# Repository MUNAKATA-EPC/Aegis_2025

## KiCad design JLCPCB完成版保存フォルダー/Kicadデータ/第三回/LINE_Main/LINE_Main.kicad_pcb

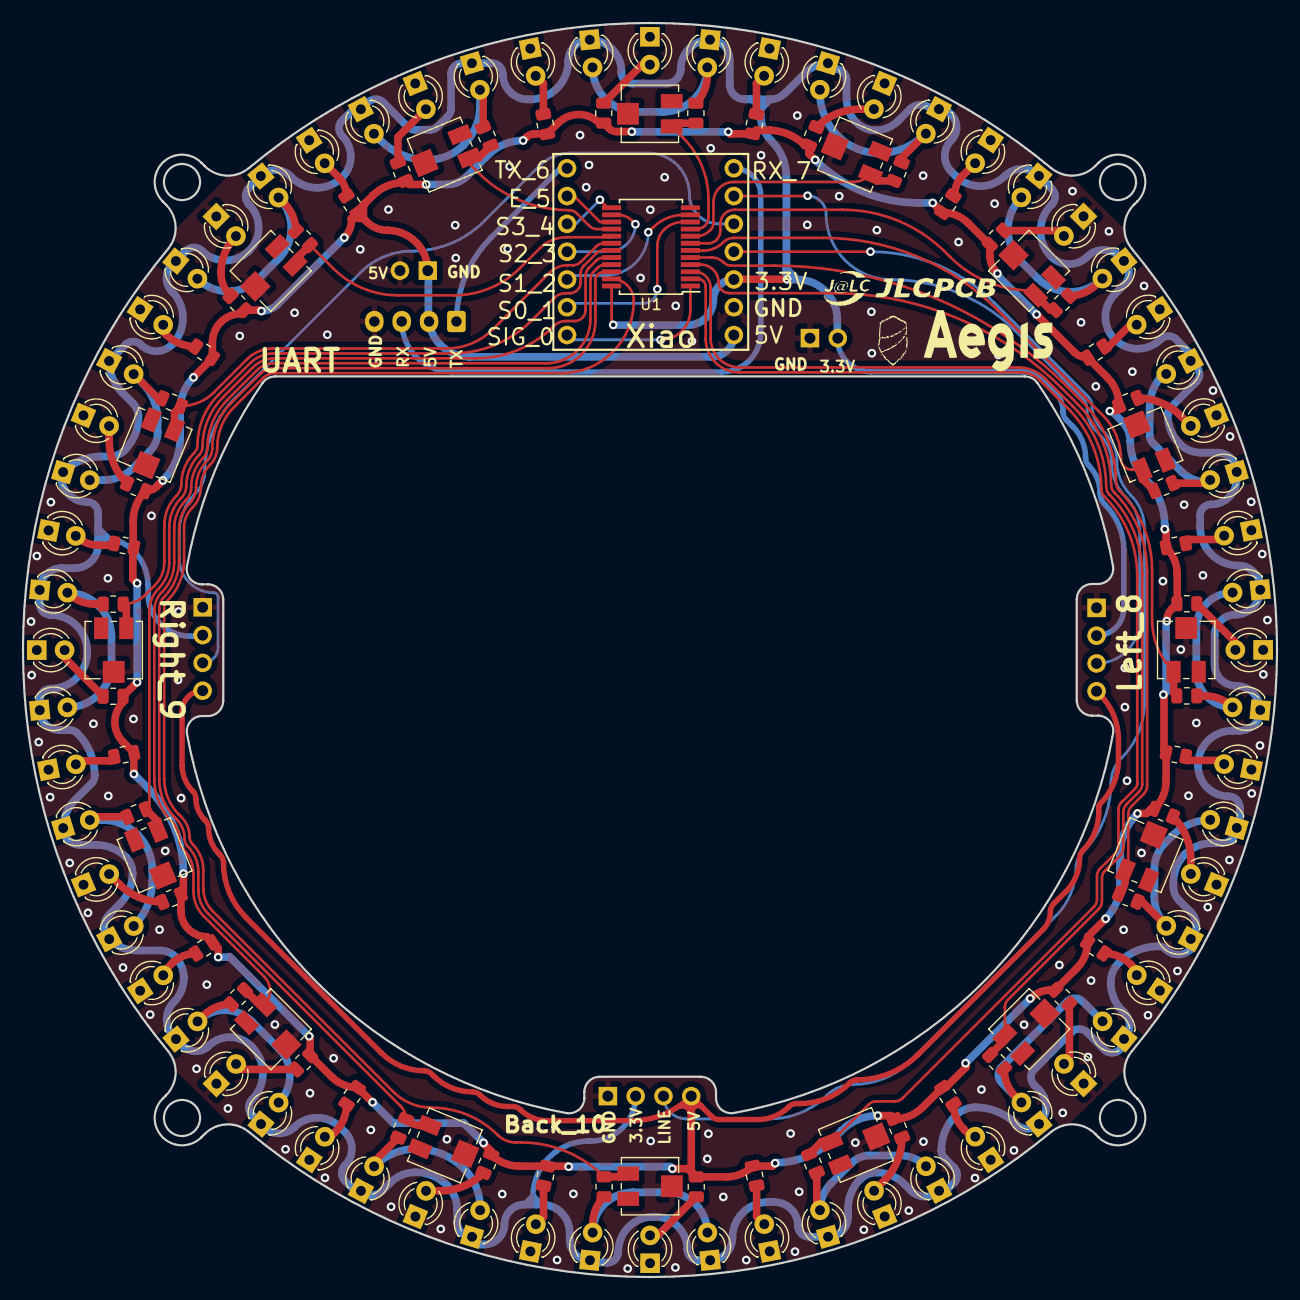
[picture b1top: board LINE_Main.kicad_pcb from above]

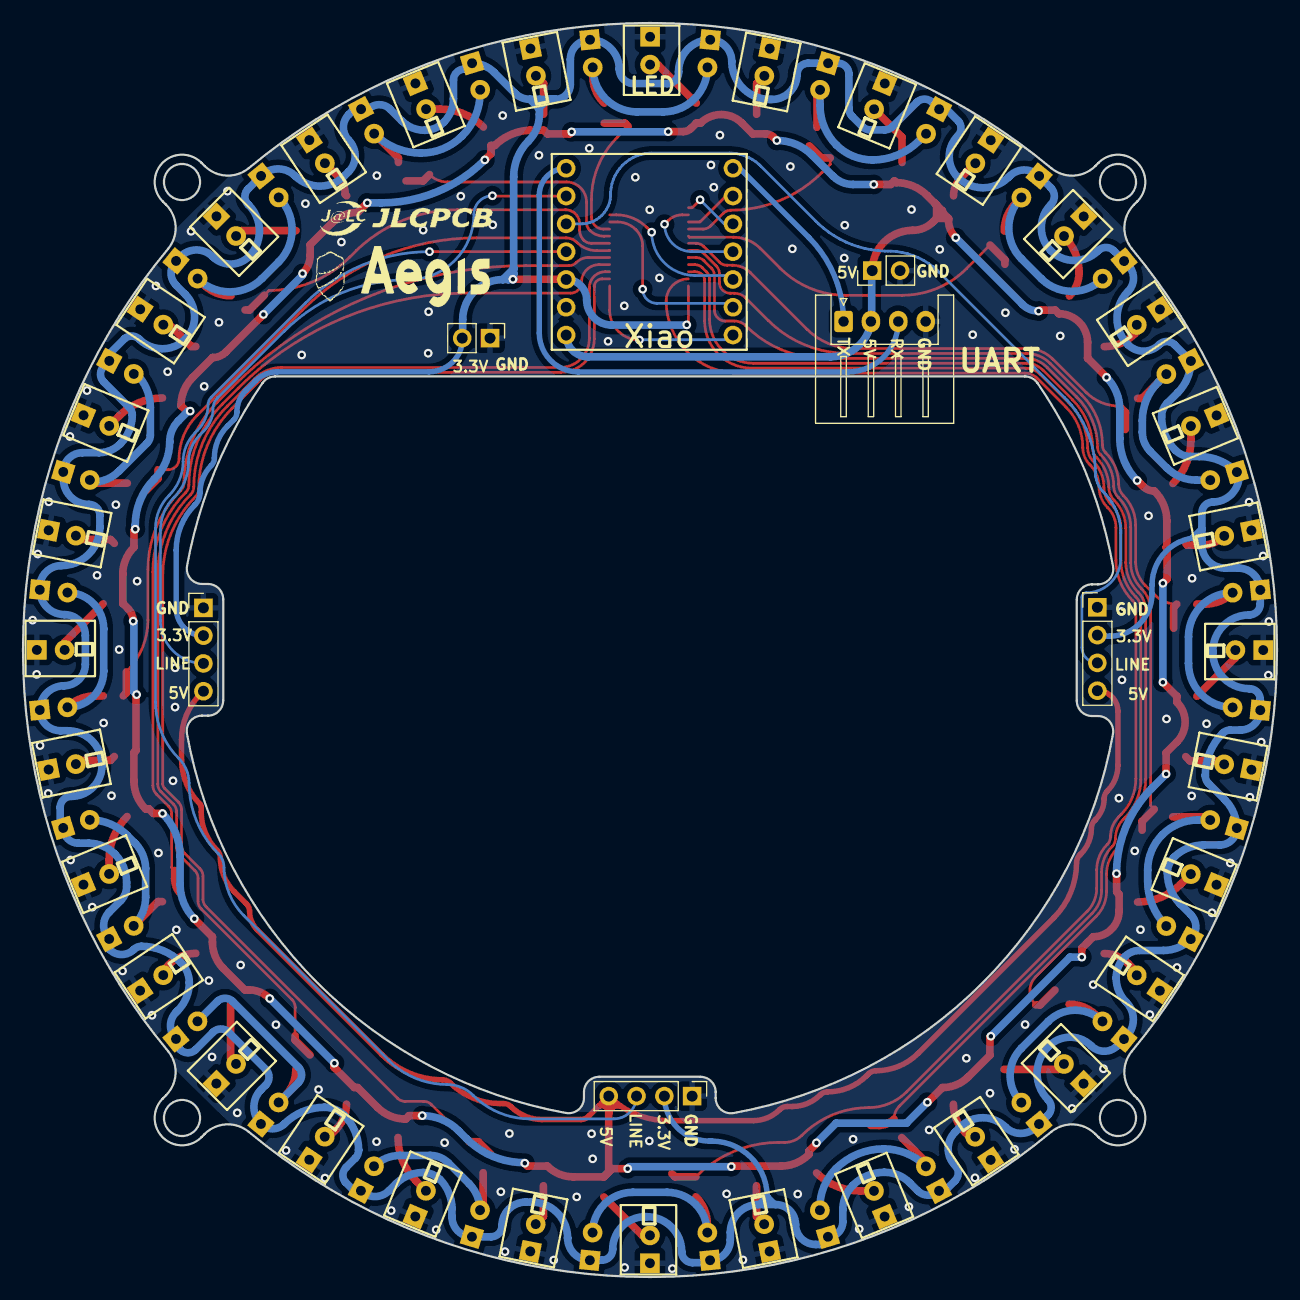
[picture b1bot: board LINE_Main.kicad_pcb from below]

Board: 2 copper layers, 114.6 x 114.6 mm, 136 parts (7 on the bottom side), 78 nets.

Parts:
C1, C2: C; PinHeader_1x02_P2.54mm_Vertical
D1, D2, D3, D4, D5, D6, D7, D8, D9, D10, D11, D12, D13, D14, D15, D16, D17, D18, D19, D20, D21, D22, D23, D24, D25, D26, D27, D28, D29, D30, D31, D32: LED; LED_D3.0mm_Clear
J1: Conn_01x04_Socket; JST_XH_S4B-XH-A_1x04_P2.50mm_Horizontal
J2, J3, J4: Conn_01x04_Socket; PinHeader_1x04_P2.54mm_Vertical
Q1, Q2, Q3, Q4, Q5, Q6, Q7, Q8, Q9, Q10, Q11, Q12, Q13, Q14, Q15, Q16, Q17, Q18, Q19, Q20, Q21, Q22, Q23, Q24, Q25, Q26, Q27, Q28, Q29, Q30, Q31, Q32: Q_Photo_NPN; LED_D3.0mm_Clear
R1, R2, R3, R4, R5, R6, R7, R8, R9, R10, R11, R12, R13, R14, R15, R16, R17, R18, R19, R20, R21, R22, R23, R24, R25, R26, R27, R28, R29, R30, R31, R32, R33, R34, R35, R36, R37, R38, R39, R40, R41, R42, R43, R44, R45, R46, R47, R48: R; R_0805_2012Metric
RV1, RV2, RV3, RV4, RV5, RV6, RV7, RV8, RV9, RV10, RV11, RV12, RV13, RV14, RV15, RV16: R_Potentiometer_Trim_US; Potentiometer_Vishay_TS53YJ_Vertical
U1: CD74HC4067SM; SSOP-24_5.3x8.2mm_P0.65mm
U2: Seeeduino_Xiao; seeeduinoXIAO

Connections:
1: R1.2, RV1.3, U1.9 (I0)
2: R2.2, RV2.3, U1.8 (I1)
3: R3.2, RV3.3, U1.7 (I2)
4: R4.2, RV4.3, U1.6 (I3)
5: R5.2, RV5.3, U1.5 (I4)
6: R6.2, RV6.3, U1.4 (I5)
7: R7.2, RV7.3, U1.3 (I6)
8: R8.2, RV8.3, U1.2 (I7)
9: R9.2, RV9.3, U1.23 (I8)
10: R10.2, RV10.3, U1.22 (I9)
11: R11.2, RV11.3, U1.21 (I10)
12: R12.2, RV12.3, U1.20 (I11)
13: R13.2, RV13.3, U1.19 (I12)
14: R14.2, RV14.3, U1.18 (I13)
15: R15.2, RV15.3, U1.17 (I14)
16: R16.2, RV16.3, U1.16 (I15)
+3.3V: C2.2, J2.2, J3.2, J4.2, Q1.1 (C), Q2.1 (C), Q3.1 (C), Q4.1 (C), Q5.1 (C), Q6.1 (C), Q7.1 (C), Q8.1 (C), Q9.1 (C), Q10.1 (C), Q11.1 (C), Q12.1 (C), Q13.1 (C), Q14.1 (C), Q15.1 (C), Q16.1 (C), Q17.1 (C), Q18.1 (C), Q19.1 (C), Q20.1 (C), Q21.1 (C), Q22.1 (C), Q23.1 (C), Q24.1 (C), Q25.1 (C), Q26.1 (C), Q27.1 (C), Q28.1 (C), Q29.1 (C), Q30.1 (C), Q31.1 (C), Q32.1 (C), U1.24 (VCC), U2.12 (3V3)
+5V: C1.1, J1.2, J2.4, J3.4, J4.4, R17.1, R18.1, R19.1, R20.1, R21.1, R22.1, R23.1, R24.1, R25.1, R26.1, R27.1, R28.1, R29.1, R30.1, R31.1, R32.1, R33.1, R34.1, R35.1, R36.1, R37.1, R38.1, R39.1, R40.1, R41.1, R42.1, R43.1, R44.1, R45.1, R46.1, R47.1, R48.1, U2.14 (5V)
Data_Line_sensor: U1.1 (COM), U2.1 (DAC)
E: U1.15 (~E), U2.6 (SCL)
GND: C1.2, C2.1, D1.1 (K), D2.1 (K), D3.1 (K), D4.1 (K), D5.1 (K), D6.1 (K), D7.1 (K), D8.1 (K), D9.1 (K), D10.1 (K), D11.1 (K), D12.1 (K), D13.1 (K), D14.1 (K), D15.1 (K), D16.1 (K), D17.1 (K), D18.1 (K), D19.1 (K), D20.1 (K), D21.1 (K), D22.1 (K), D23.1 (K), D24.1 (K), D25.1 (K), D26.1 (K), D27.1 (K), D28.1 (K), D29.1 (K), D30.1 (K), D31.1 (K), D32.1 (K), J1.4, J2.1, J3.1, J4.1, RV1.2, RV2.2, RV3.2, RV4.2, RV5.2, RV6.2, RV7.2, RV8.2, RV9.2, RV10.2, RV11.2, RV12.2, RV13.2, RV14.2, RV15.2, RV16.2, U1.12 (GND), U2.13 (GND)
Line_RX: J1.3, U2.8 (RX)
Line_TX: J1.1, U2.7 (TX)
unnamed: D1.2 (A), R17.2
unnamed: D2.2 (A), R18.2
unnamed: D3.2 (A), R19.2
unnamed: D4.2 (A), R20.2
unnamed: D5.2 (A), R21.2
unnamed: D6.2 (A), R22.2
unnamed: D7.2 (A), R23.2
unnamed: D8.2 (A), R24.2
unnamed: D9.2 (A), R25.2
unnamed: D10.2 (A), R26.2
unnamed: D11.2 (A), R27.2
unnamed: D12.2 (A), R28.2
unnamed: D13.2 (A), R29.2
unnamed: D14.2 (A), R30.2
unnamed: D15.2 (A), R31.2
unnamed: D16.2 (A), R32.2
unnamed: D17.2 (A), R33.2
unnamed: D18.2 (A), R34.2
unnamed: D19.2 (A), R35.2
unnamed: D20.2 (A), R36.2
unnamed: D21.2 (A), R37.2
unnamed: D22.2 (A), R38.2
unnamed: D23.2 (A), R39.2
unnamed: D24.2 (A), R40.2
unnamed: D25.2 (A), R41.2
unnamed: D26.2 (A), R42.2
unnamed: D27.2 (A), R43.2
unnamed: D28.2 (A), R44.2
unnamed: D29.2 (A), R45.2
unnamed: D30.2 (A), R46.2
unnamed: D31.2 (A), R47.2
unnamed: D32.2 (A), R48.2
unnamed: Q1.2 (E), Q2.2 (E), R1.1
unnamed: Q3.2 (E), Q4.2 (E), R2.1
unnamed: Q5.2 (E), Q6.2 (E), R3.1
unnamed: Q7.2 (E), Q8.2 (E), R4.1
unnamed: Q9.2 (E), Q10.2 (E), R5.1
unnamed: Q11.2 (E), Q12.2 (E), R6.1
unnamed: Q13.2 (E), Q14.2 (E), R7.1
unnamed: Q15.2 (E), Q16.2 (E), R8.1
unnamed: Q17.2 (E), Q18.2 (E), R9.1
unnamed: Q19.2 (E), Q20.2 (E), R10.1
unnamed: Q21.2 (E), Q22.2 (E), R11.1
unnamed: Q23.2 (E), Q24.2 (E), R12.1
unnamed: Q25.2 (E), Q26.2 (E), R13.1
unnamed: Q27.2 (E), Q28.2 (E), R14.1
unnamed: Q29.2 (E), Q30.2 (E), R15.1
unnamed: Q31.2 (E), Q32.2 (E), R16.1
S0: U1.10 (S0), U2.2
S1: U1.11 (S1), U2.3
S3: U1.14 (S2), U2.4
S4: U1.13 (S3), U2.5 (SDA)
Sensor_Back: J2.3, U2.11 (MOSI)
Sensor_Left: J4.3, U2.9 (SCK)
Sensor_Right: J3.3, U2.10 (MISO)

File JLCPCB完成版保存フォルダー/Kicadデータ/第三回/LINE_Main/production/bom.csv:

Designator,Footprint,Quantity,Value,LCSC Part #
"C1, C2",PinHeader_1x02_P2.54mm_Vertical,2,C,
"D1, D10, D11, D12, D13, D14, D15, D16, D17, D18, D19, D2, D20, D21, D22, D23, D24, D25, D26, D27, D28, D29, D3, D30, D31, D32, D4, D5, D6, D7, D8, D9",LED_D3.0mm_Clear,32,LED,
J1,JST_XH_S4B-XH-A_1x04_P2.50mm_Horizontal,1,Conn_01x04_Socket,
"J2, J3, J4",PinHeader_1x04_P2.54mm_Vertical,3,Conn_01x04_Socket,
"Q1, Q10, Q11, Q12, Q13, Q14, Q15, Q16, Q17, Q18, Q19, Q2, Q20, Q21, Q22, Q23, Q24, Q25, Q26, Q27, Q28, Q29, Q3, Q30, Q31, Q32, Q4, Q5, Q6, Q7, Q8, Q9",LED_D3.0mm_Clear,32,Q_Photo_NPN,
"R1, R10, R11, R12, R13, R14, R15, R16, R17, R18, R19, R2, R20, R21, R22, R23, R24, R25, R26, R27, R28, R29, R3, R30, R31, R32, R33, R34, R35, R36, R37, R38, R39, R4, R40, R41, R42, R43, R44, R45, R46, R47, R48, R5, R6, R7, R8, R9",0805,48,R,
"RV1, RV10, RV11, RV12, RV13, RV14, RV15, RV16, RV2, RV3, RV4, RV5, RV6, RV7, RV8, RV9",Potentiometer_Vishay_TS53YJ_Vertical,16,R_Potentiometer_Trim_US,
U1,SSOP-24_5.3x8.2mm_P0.65mm,1,CD74HC4067SM,
U2,seeeduinoXIAO,1,Seeeduino_Xiao,

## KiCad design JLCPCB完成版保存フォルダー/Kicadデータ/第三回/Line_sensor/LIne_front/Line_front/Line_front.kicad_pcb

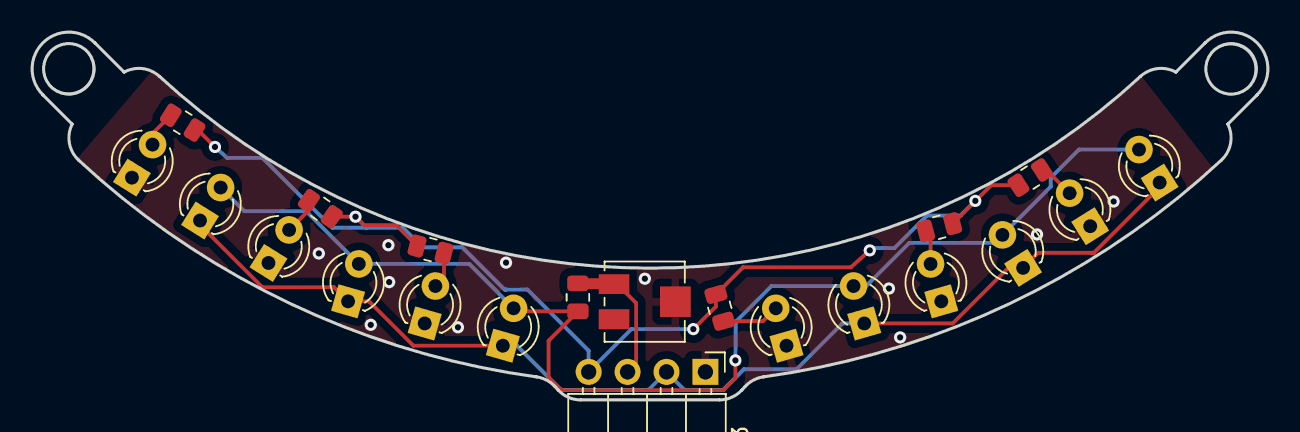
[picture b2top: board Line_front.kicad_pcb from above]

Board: 2 copper layers, 80.7 x 24.0 mm, 21 parts (0 on the bottom side), 11 nets.

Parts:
D1, D2, D2#2, D3, D4, D7: LED; LED_D3.0mm_Clear
J3: Conn_01x04_Socket; PinHeader_1x04_P2.54mm_Horizontal
Q1, Q3, Q4, Q15, Q16, Q17: Q_Photo_NPN; LED_D3.0mm_Clear
R1, R1#2, R2, R4, R5, R6, R7: R; R_0805_2012Metric
RV2: R_Potentiometer_Trim_US; Potentiometer_Vishay_TS53YJ_Vertical

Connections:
+3.3V: J3.2, Q1.1 (C), Q3.1 (C), Q4.1 (C), Q15.1 (C), Q16.1 (C), Q17.1 (C)
+5V: J3.4, R1.1, R1#2.1, R2.1, R5.1, R6.1, R7.1
Data_Line_sensor: J3.3, R4.2, RV2.3
GND: D1.1 (K), D2.1 (K), D2#2.1 (K), D3.1 (K), D4.1 (K), D7.1 (K), J3.1, RV2.2
unnamed: D1.2 (A), R1#2.2
unnamed: D2#2.2 (A), R5.2
unnamed: D3.2 (A), R6.2
unnamed: D4.2 (A), R7.2
unnamed: D7.2 (A), R2.2
unnamed: D2.2 (A), R1.2
unnamed: Q1.2 (E), Q3.2 (E), Q4.2 (E), Q15.2 (E), Q16.2 (E), Q17.2 (E), R4.1

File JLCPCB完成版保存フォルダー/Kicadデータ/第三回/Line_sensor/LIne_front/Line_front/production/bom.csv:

Designator,Footprint,Quantity,Value,LCSC Part #
"D1, D2_2, D2, D3, D4, D7",LED_D3.0mm_Clear,6,LED,
J3,PinHeader_1x04_P2.54mm_Vertical,1,Conn_01x04_Socket,
"Q1, Q15, Q16, Q17, Q3, Q4",LED_D3.0mm_Clear,6,Q_Photo_NPN,
"R1_2, R1, R2, R4, R5, R6, R7",0805,7,R,
RV2,Potentiometer_Vishay_TS53YJ_Vertical,1,R_Potentiometer_Trim_US,

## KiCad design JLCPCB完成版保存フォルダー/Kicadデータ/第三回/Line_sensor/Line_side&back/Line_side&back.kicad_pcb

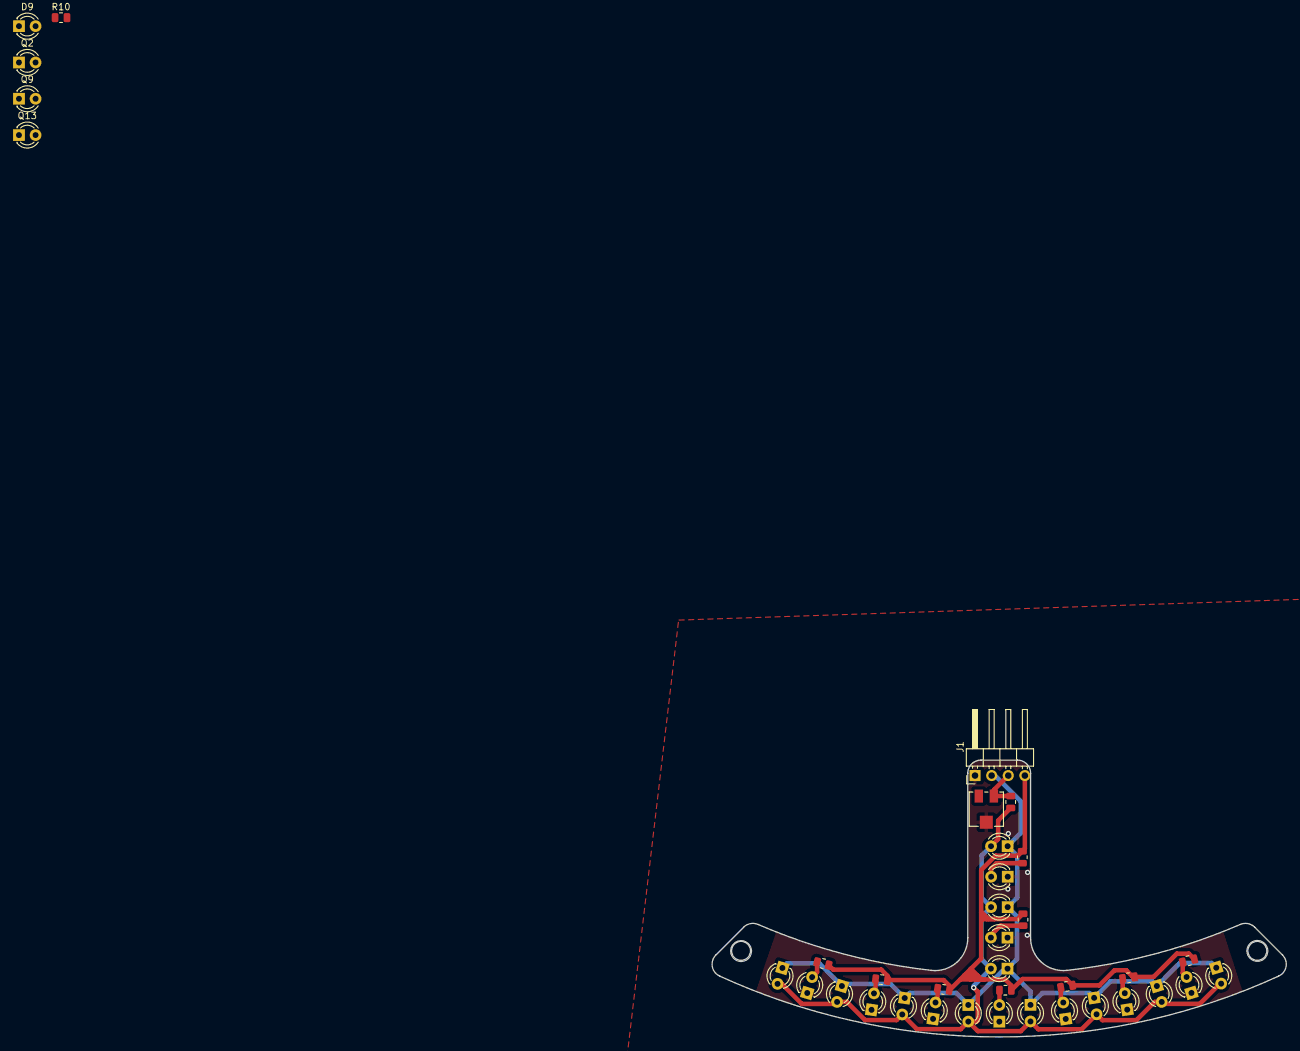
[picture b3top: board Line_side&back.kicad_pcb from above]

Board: 2 copper layers, 87.8 x 42.3 mm, 37 parts (0 on the bottom side), 15 nets.

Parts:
D1, D2, D3, D4, D5, D6, D7, D8, D9, D10: LED; LED_D3.0mm_Clear
J1: Conn_01x04_Socket; PinHeader_1x04_P2.54mm_Horizontal
Q1, Q2, Q3, Q4, Q5, Q6, Q7, Q8, Q9, Q10, Q13, Q14, Q15, Q16: Q_Photo_NPN; LED_D3.0mm_Clear
R1, R2, R3, R4, R5, R6, R7, R8, R9, R10, R11: R; R_0805_2012Metric
RV1: R_Potentiometer_Trim_US; Potentiometer_Vishay_TS53YJ_Vertical

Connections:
+3.3V: J1.2, Q1.1 (C), Q2.1 (C), Q3.1 (C), Q4.1 (C), Q5.1 (C), Q6.1 (C), Q7.1 (C), Q8.1 (C), Q9.1 (C), Q10.1 (C), Q13.1 (C), Q14.1 (C), Q15.1 (C), Q16.1 (C)
+5V: J1.4, R1.1, R2.1, R4.1, R5.1, R6.1, R7.1, R8.1, R9.1, R10.1, R11.1
Data_Line_sensor: J1.3, R3.2, RV1.3
GND: D1.1 (K), D2.1 (K), D3.1 (K), D4.1 (K), D5.1 (K), D6.1 (K), D7.1 (K), D8.1 (K), D9.1 (K), D10.1 (K), J1.1, RV1.2
unnamed: D1.2 (A), R1.2
unnamed: D2.2 (A), R2.2
unnamed: D3.2 (A), R4.2
unnamed: D4.2 (A), R5.2
unnamed: D5.2 (A), R6.2
unnamed: D6.2 (A), R7.2
unnamed: D7.2 (A), R8.2
unnamed: D8.2 (A), R9.2
unnamed: D9.2 (A), R10.2
unnamed: D10.2 (A), R11.2
unnamed: Q1.2 (E), Q2.2 (E), Q3.2 (E), Q4.2 (E), Q5.2 (E), Q6.2 (E), Q7.2 (E), Q8.2 (E), Q9.2 (E), Q10.2 (E), Q13.2 (E), Q14.2 (E), Q15.2 (E), Q16.2 (E), R3.1

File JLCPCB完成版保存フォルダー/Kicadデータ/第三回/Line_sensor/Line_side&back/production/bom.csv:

Designator,Footprint,Quantity,Value,LCSC Part #
"D1, D10, D2, D3, D4, D5, D6, D7, D8",LED_D3.0mm_Clear,9,LED,
J1,PinHeader_1x04_P2.54mm_Vertical,1,Conn_01x04_Socket,
"Q1, Q10, Q14, Q15, Q16, Q3, Q4, Q5, Q6, Q7, Q8",LED_D3.0mm_Clear,11,Q_Photo_NPN,
"R1, R11, R2, R3, R4, R5, R6, R7, R8, R9",0805,10,R,
RV1,Potentiometer_Vishay_TS53YJ_Vertical,1,R_Potentiometer_Trim_US,

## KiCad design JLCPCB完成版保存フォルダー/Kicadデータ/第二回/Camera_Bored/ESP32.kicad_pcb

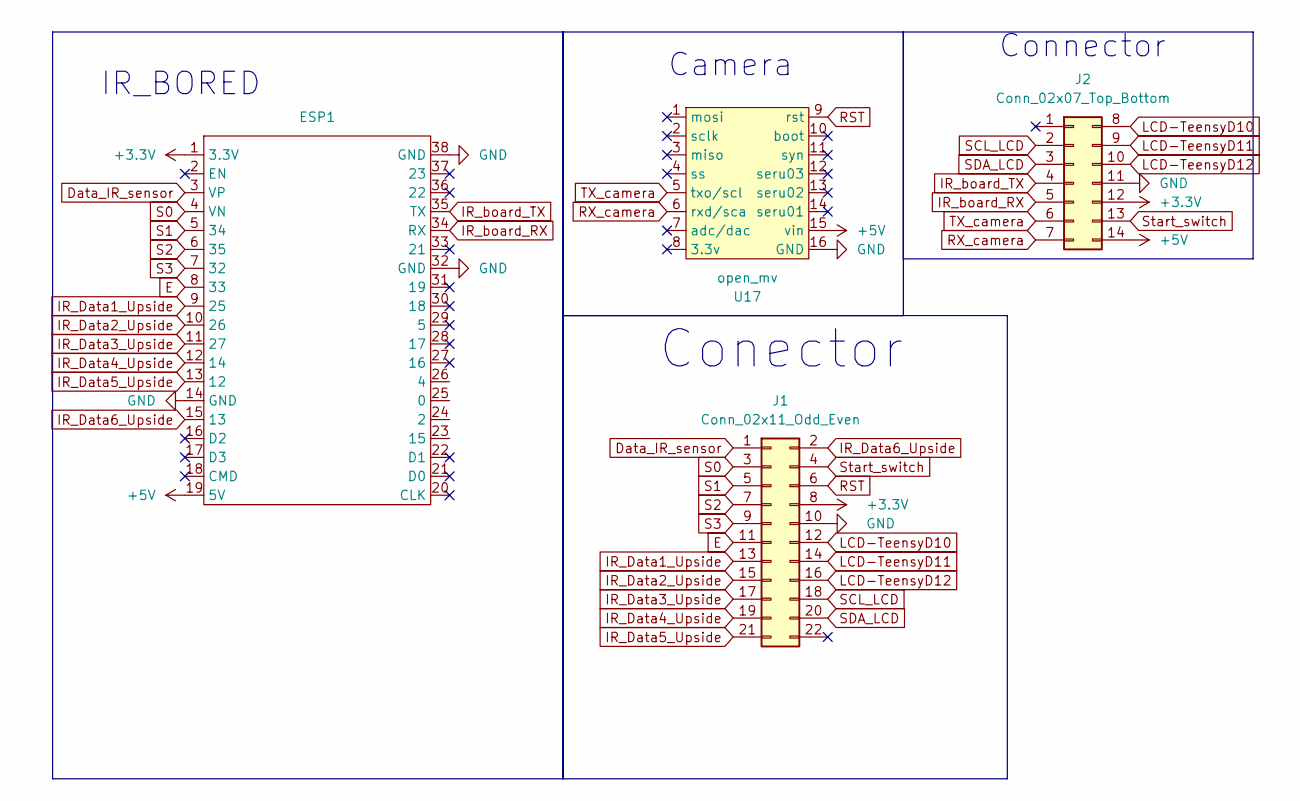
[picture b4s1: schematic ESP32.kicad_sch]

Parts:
ESP1: ESP32-DevKitC
J1: Conn_02x11_Odd_Even; PinHeader_2x11_P2.54mm_Vertical
J2: Conn_02x07_Top_Bottom; IDC-Header_2x07_P2.54mm_Vertical
U17: open_mv; OpenMV

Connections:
+3.3V: ESP1.1 (3.3V), J1.8, J2.12
+5V: ESP1.19 (5V), J2.14, U17.15 (vin)
Data_IR_sensor: ESP1.3 (VP), J1.1
E: ESP1.8 (33), J1.11
GND: ESP1.14 (GND), ESP1.32 (GND), ESP1.38 (GND), J1.10, J2.11, U17.16 (GND)
IR_Data1_Upside: ESP1.9 (25), J1.13
IR_Data2_Upside: ESP1.10 (26), J1.15
IR_Data3_Upside: ESP1.11 (27), J1.17
IR_Data4_Upside: ESP1.12 (14), J1.19
IR_Data5_Upside: ESP1.13 (12), J1.21
IR_Data6_Upside: ESP1.15 (13), J1.2
IR_board_RX: ESP1.34 (RX), J2.5
IR_board_TX: ESP1.35 (TX), J2.4
LCD-TeensyD10: J1.12, J2.8
LCD-TeensyD11: J1.14, J2.9
LCD-TeensyD12: J1.16, J2.10
RST: J1.6, U17.9 (rst)
RX_camera: J2.7, U17.6 (rxd/sca)
S0: ESP1.4 (VN), J1.3
S1: ESP1.5 (34), J1.5
S2: ESP1.6 (35), J1.7
S3: ESP1.7 (32), J1.9
SCL_LCD: J1.18, J2.2
SDA_LCD: J1.20, J2.3
Start_switch: J1.4, J2.13
TX_camera: J2.6, U17.5 (txo/scl)

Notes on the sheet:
Connector
Conector
IR_BORED
Camera

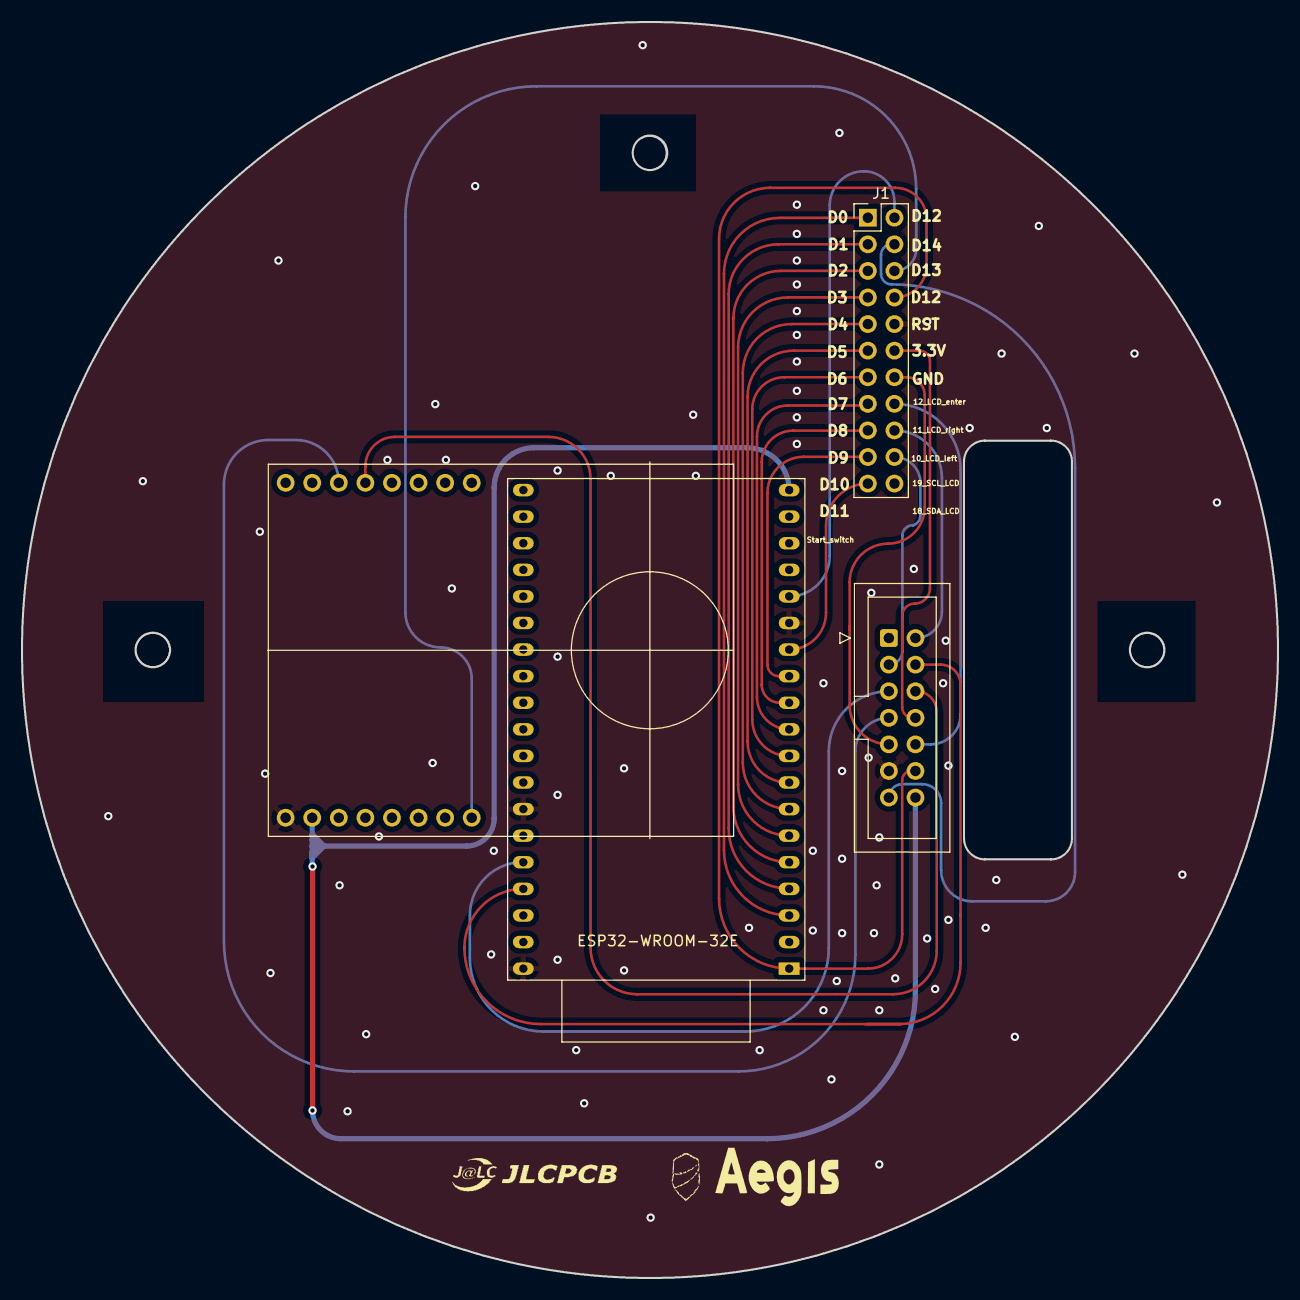
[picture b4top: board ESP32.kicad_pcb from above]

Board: 2 copper layers, 120.0 x 120.0 mm, 4 parts (0 on the bottom side), 26 nets.

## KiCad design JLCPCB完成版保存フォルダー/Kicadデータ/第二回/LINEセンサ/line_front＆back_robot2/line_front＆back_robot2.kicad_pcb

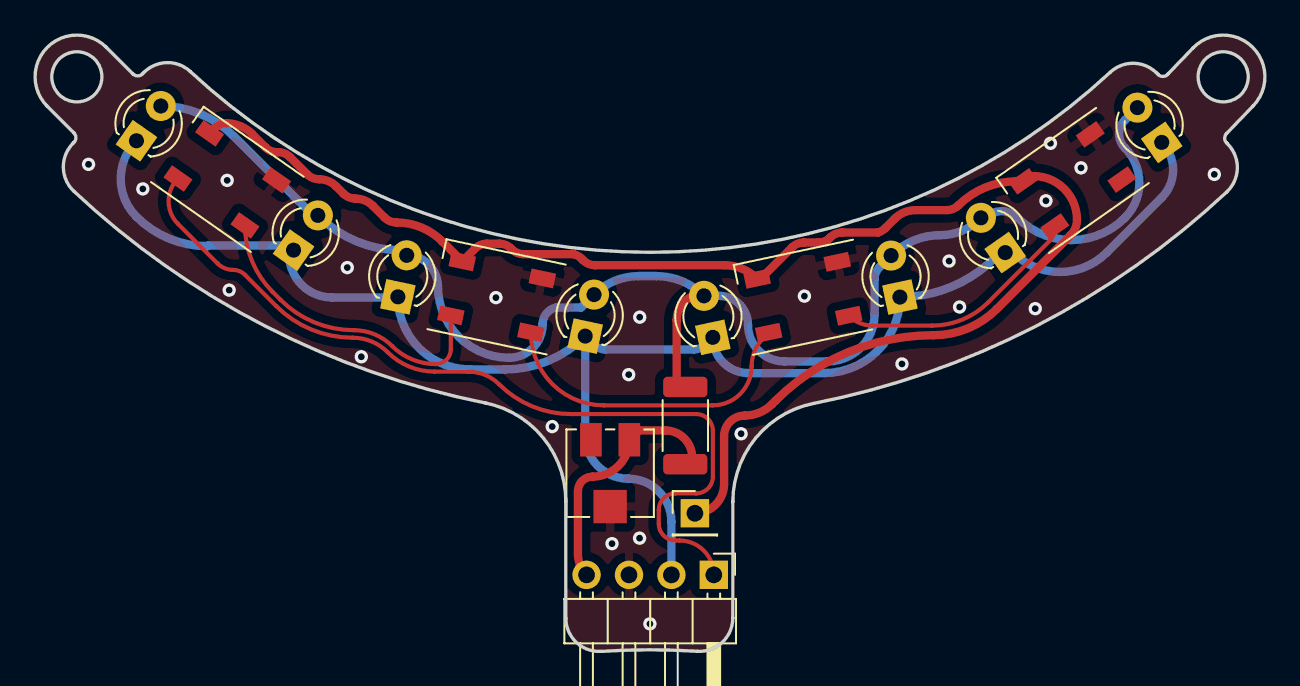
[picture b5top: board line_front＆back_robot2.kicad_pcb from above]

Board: 2 copper layers, 73.6 x 36.9 mm, 16 parts (0 on the bottom side), 9 nets.

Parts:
D1, D2, D3, D5: NeoPixel_THT; LED_WS2812B_PLCC4_5.0x5.0mm_P3.2mm
J2: Conn_01x04_Pin; PinHeader_1x04_P2.54mm_Horizontal
J3: Conn_01x01_Pin; PinHeader_1x01_P2.54mm_Vertical
Q1, Q2, Q3, Q4, Q7, Q8, Q9, Q10: Q_Photo_NPN; LED_D3.0mm_Clear
R8: 1K; R_2010_5025Metric
RV2: R_Potentiometer_Trim_US; Potentiometer_Vishay_TS53YJ_Vertical

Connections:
+3.3V: J2.2, Q1.1 (C), Q2.1 (C), Q3.1 (C), Q4.1 (C), Q7.1 (C), Q8.1 (C), Q9.1 (C), Q10.1 (C)
+5V: D1.3 (VDD), D2.3 (VDD), D3.3 (VDD), D5.3 (VDD), J3.1
/PWM: D3.4 (DIN), J2.1
/S: J2.4, R8.1, RV2.3
GND: D1.2 (GND), D2.2 (GND), D3.2 (GND), D5.2 (GND), J2.3, RV2.2
unnamed: D1.4 (DIN), D5.1 (DOUT)
unnamed: D2.4 (DIN), D3.1 (DOUT)
unnamed: D2.1 (DOUT), D5.4 (DIN)
unnamed: Q1.2 (E), Q2.2 (E), Q3.2 (E), Q4.2 (E), Q7.2 (E), Q8.2 (E), Q9.2 (E), Q10.2 (E), R8.2

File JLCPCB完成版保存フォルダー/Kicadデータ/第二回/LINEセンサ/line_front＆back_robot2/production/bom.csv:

Designator,Footprint,Quantity,Value,LCSC Part #
"D1, D2, D3, D5",LED_WS2812B_PLCC4_5.0x5.0mm_P3.2mm,4,NeoPixel_THT,
J2,PinHeader_1x04_P2.54mm_Horizontal,1,Conn_01x04_Pin,
J3,PinHeader_1x01_P2.54mm_Vertical,1,Conn_01x01_Pin,
"Q1, Q10, Q2, Q3, Q4, Q7, Q8, Q9",LED_D3.0mm_Clear,8,Q_Photo_NPN,
R8,2010,1,1K,
RV2,Potentiometer_Vishay_TS53YJ_Vertical,1,R_Potentiometer_Trim_US,

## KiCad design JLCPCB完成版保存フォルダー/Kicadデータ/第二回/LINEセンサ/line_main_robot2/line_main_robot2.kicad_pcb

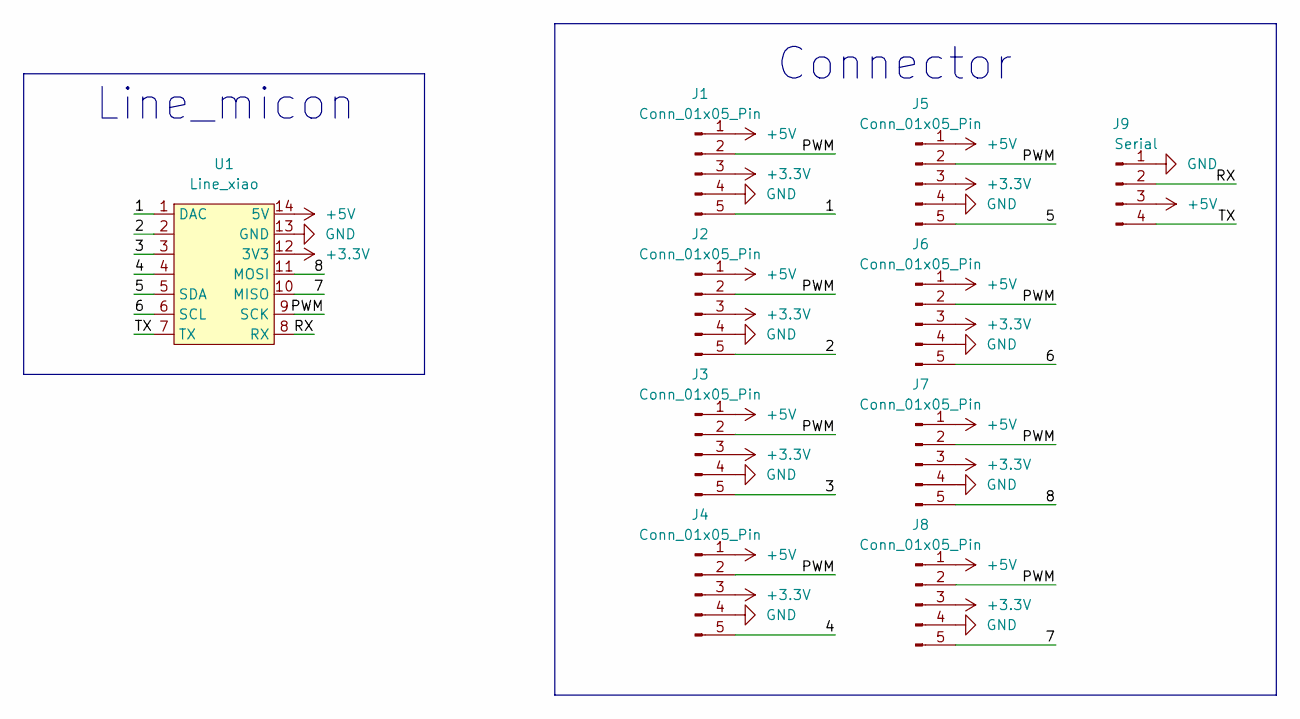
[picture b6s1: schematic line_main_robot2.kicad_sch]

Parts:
J1, J2, J3, J4, J5, J6, J7, J8: Conn_01x05_Pin; PinSocket_1x05_P2.54mm_Horizontal
J9: Serial; JST_XH_S4B-XH-A_1x04_P2.50mm_Horizontal
U1: Line_xiao; seeeduinoXIAO

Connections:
+3.3V: J1.3, J2.3, J3.3, J4.3, J5.3, J6.3, J7.3, J8.3, U1.12 (3V3)
+5V: J1.1, J2.1, J3.1, J4.1, J5.1, J6.1, J7.1, J8.1, J9.3, U1.14 (5V)
/1: J1.5, U1.1 (DAC)
/2: J2.5, U1.2
/3: J3.5, U1.3
/4: J4.5, U1.4
/5: J5.5, U1.5 (SDA)
/6: J6.5, U1.6 (SCL)
/7: J8.5, U1.10 (MISO)
/8: J7.5, U1.11 (MOSI)
/PWM: J1.2, J2.2, J3.2, J4.2, J5.2, J6.2, J7.2, J8.2, U1.9 (SCK)
/RX: J9.2, U1.8 (RX)
/TX: J9.4, U1.7 (TX)
GND: J1.4, J2.4, J3.4, J4.4, J5.4, J6.4, J7.4, J8.4, J9.1, U1.13 (GND)

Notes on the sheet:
Connector
Line_micon

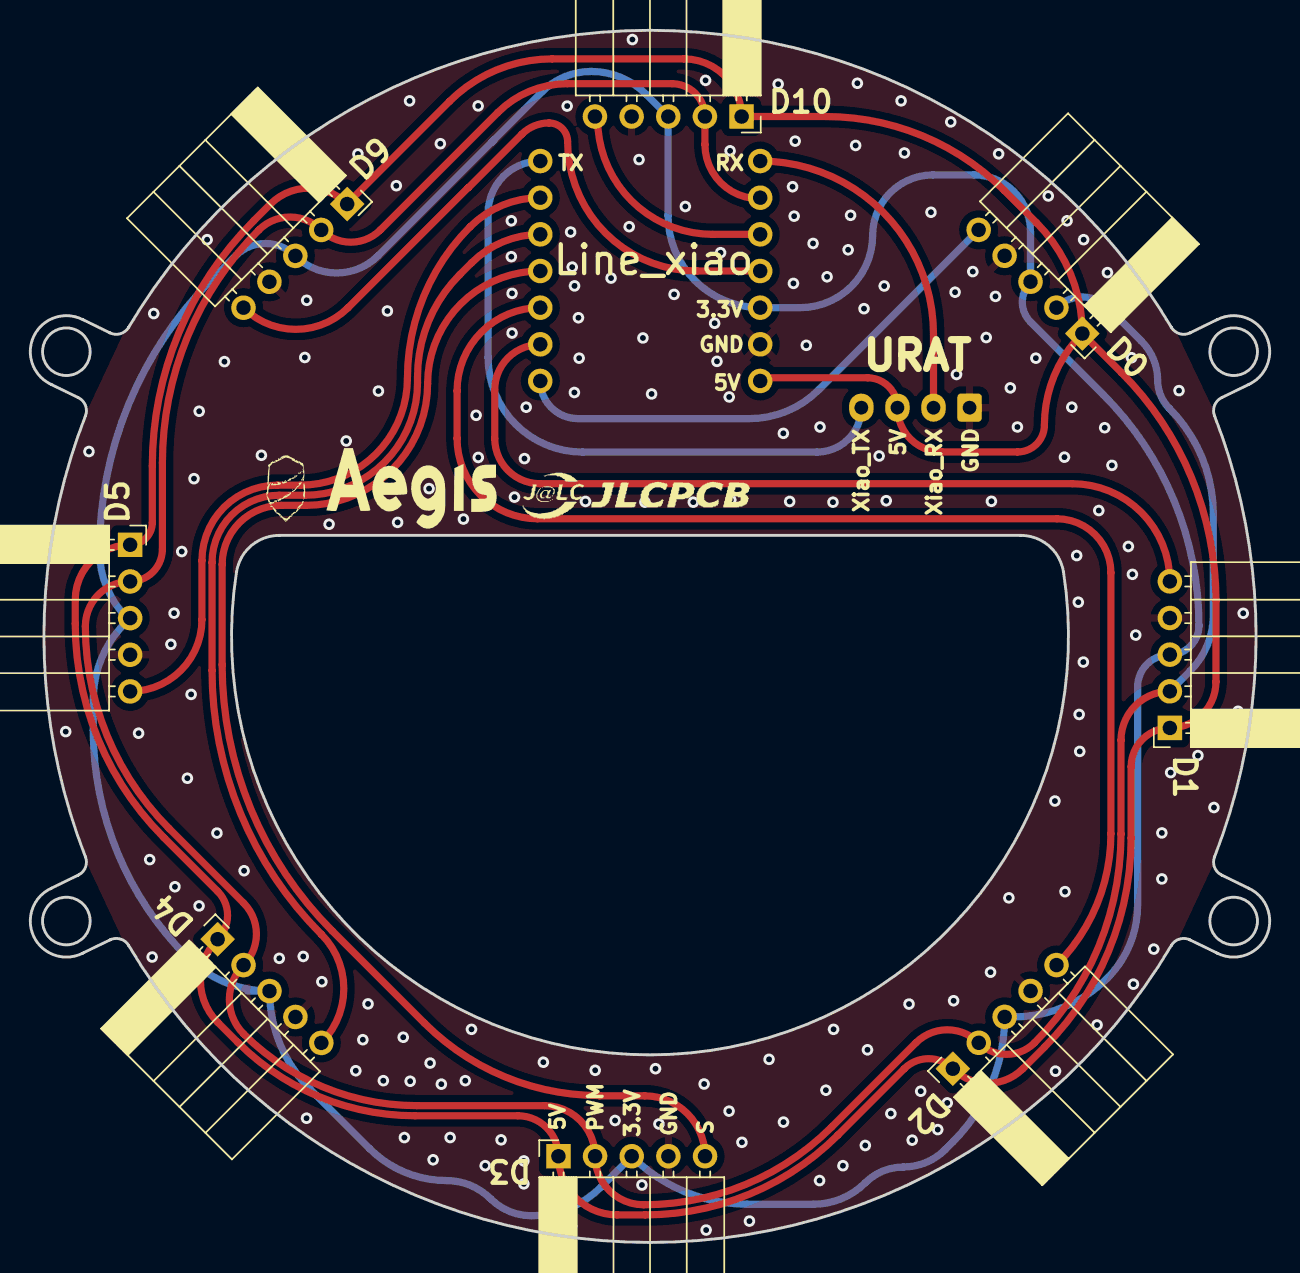
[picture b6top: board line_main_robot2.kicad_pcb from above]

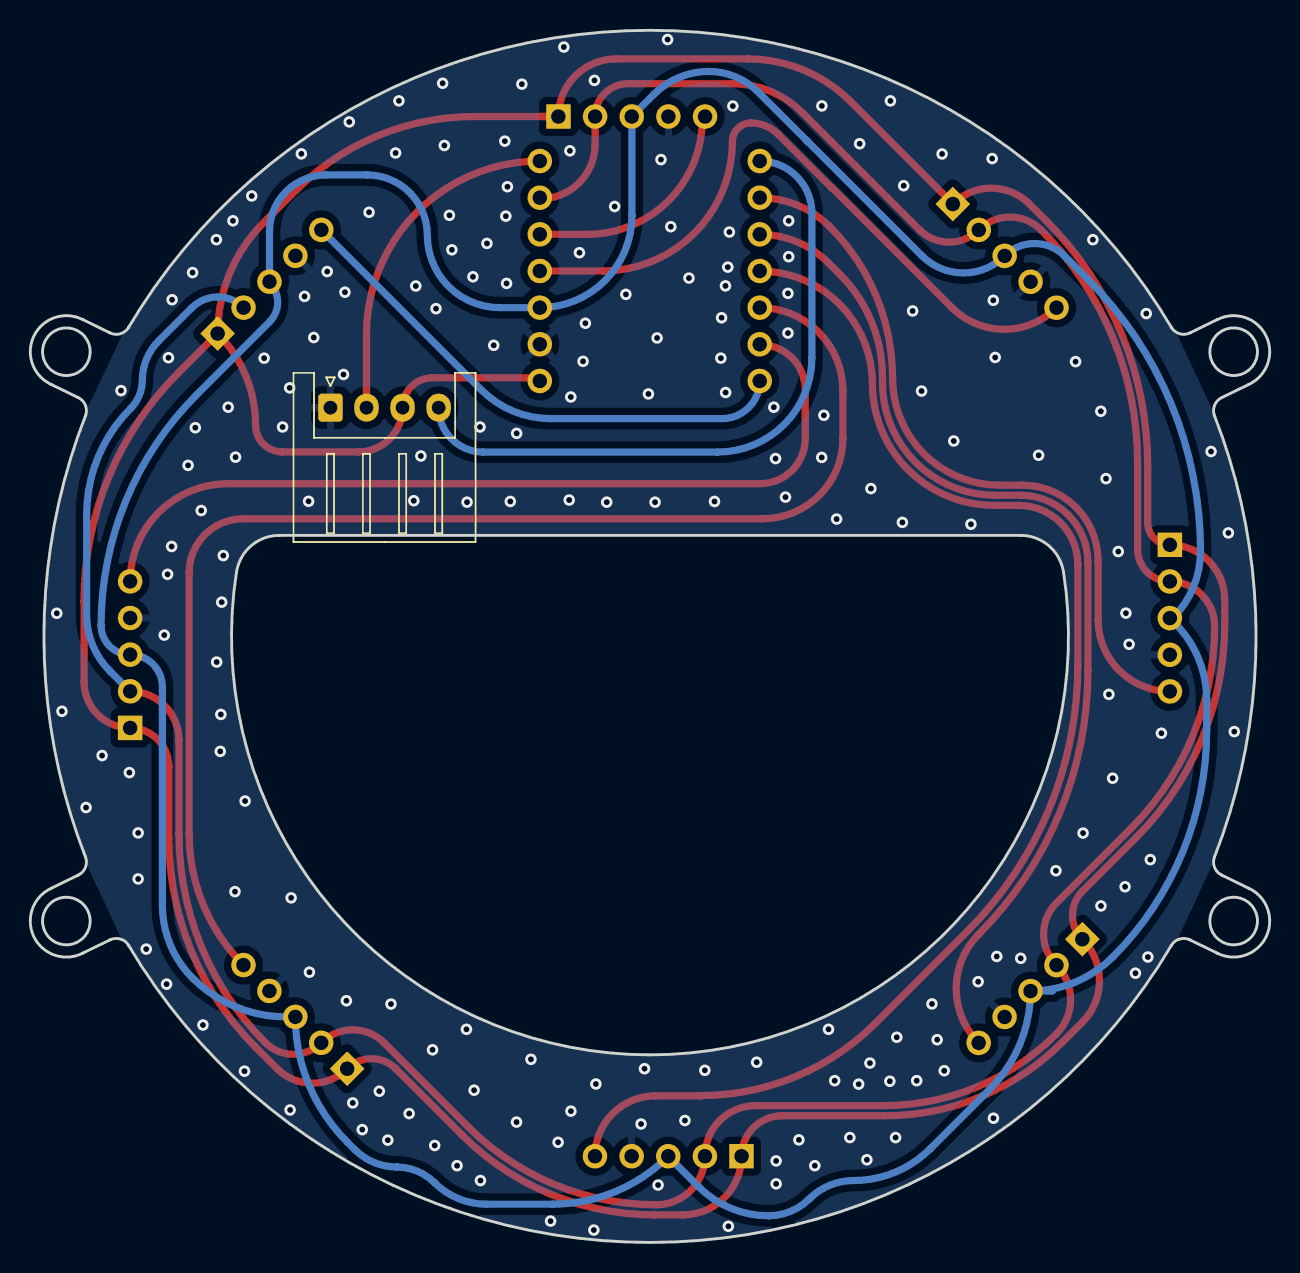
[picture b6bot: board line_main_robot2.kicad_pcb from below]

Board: 2 copper layers, 85.9 x 84.0 mm, 10 parts (2 on the bottom side), 14 nets.
